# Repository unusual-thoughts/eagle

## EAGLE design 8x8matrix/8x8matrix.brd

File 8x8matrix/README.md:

Backpack for 8x8 RGB LED matrix
==============================

This is a simple breakout board for 8x8 RGB matrices like the [GTM2088ARGB](http://www.ebay.com/itm/5mm-8x8-Matrix-RGB-LED-Common-Anode-Full-Colour-60-60mm-/370699782315)  
It uses TLC5947 that provides 24 12 bit current sink PWM channels, and a 74HC138 3 to 8 line decoder followed by P-channel MOSFETs to drive the rows.
The parts are in the ../mylibs/mylib.lbr library.  
The whole thing fits on a single layer PCB.  
The matrix is controlled through the 9-pin header with this pinout:

Pin number	| Label	| Description
----------	| -----	| -----------
1			| A2	| row higher bit
2			| A1	| row middle bit
3			| A0	| row lower bit
4			| SIN	| TLC data (24x12 bit = 36 bytes)
5			| SCLK	| TLC clock
6			| BLANK	| TLC blank columns and reset PWM timer
7			| GND	| Ground
8			| VCC	| +5V
9			| XLAT	| TLC latch data

To get everything to fit on a single sided board, I had to make weird column and row assignments:

A0	| A1	| A2	| Row Number
--- | ---	| ---	| ----------
0	| 0		| 0		| 2
0	| 0		| 1		| 1
0	| 1		| 0		| 0
0	| 1		| 1		| 7
1	| 0		| 0		| 4
1	| 0		| 1		| 5
1	| 1		| 0		| 6
1	| 1		| 1		| 3

TLC channel	| Columns
----------  | ------
0-7			| Red 0-7
8-15		| Blue 0-7
16-23		| Green 7-0 (inverted order)

There is a modified version of the Tlc5940 library by Alex Leone, named Tlc5947 in my arduino folder. Like its counterpart, it can use arduino hardware spi to speed things up to an acceptable refresh rate. The basic bitbang code flickers quite a bit, even with direct port manipulation.

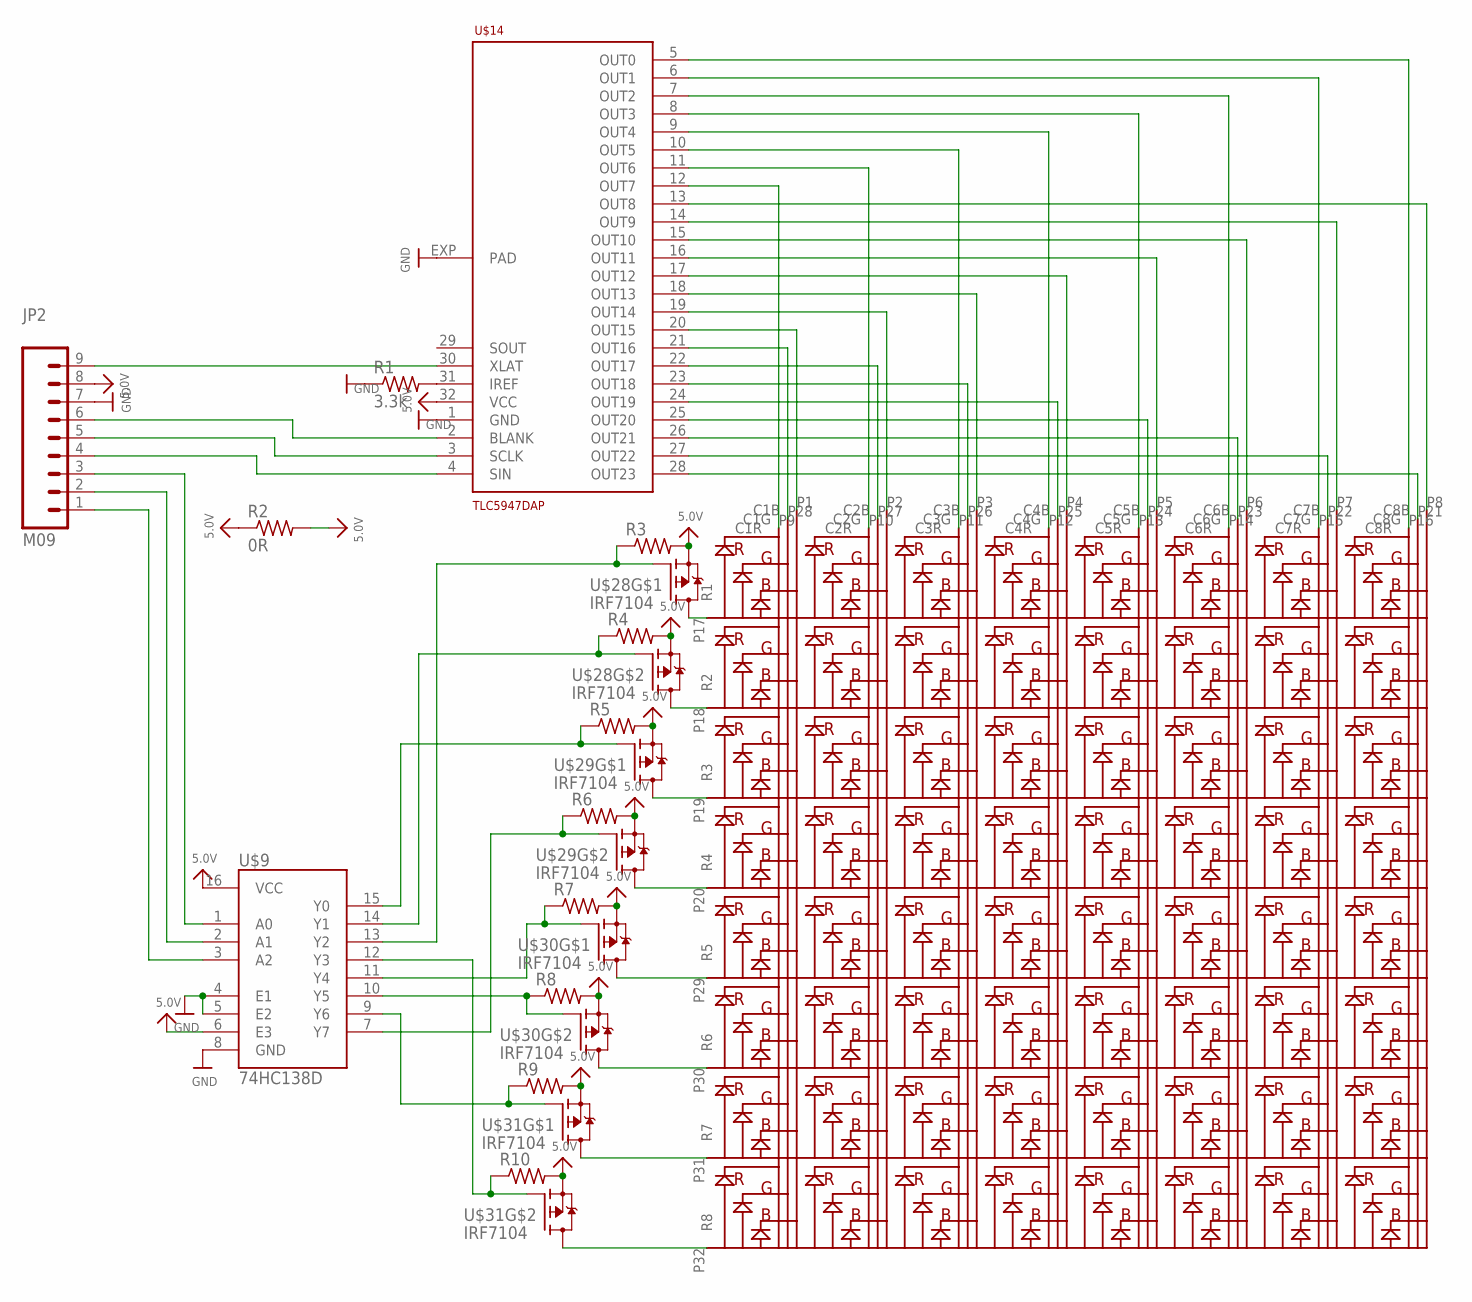
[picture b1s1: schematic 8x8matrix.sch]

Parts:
JP2: M09; 1X09
R1: 3.3k; R0805
R2: 0R; M1206
R3, R4, R5, R6, R7, R8, R9, R10: R-US_R0805; R0805
U$1: GTM2088ARGB; 8X8MATRIX
U$9: 74HC138D; SO-16
U$14: TLC5947DAP; HTSSOP32DAP
U$28, U$29, U$30, U$31: IRF7104; SOIC8

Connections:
5.0V: JP2.8, R2.1, R2.2, R3.2, R4.2, R5.2, R6.2, R7.2, R8.2, R9.2, R10.2, U$9.6 (E3), U$9.16 (VCC), U$14.32 (VCC), U$28.1 (S), U$28.3 (S), U$29.1 (S), U$29.3 (S), U$30.1 (S), U$30.3 (S), U$31.1 (S), U$31.3 (S)
BLANK: JP2.6, U$14.2 (BLANK)
GND: JP2.7, R1.1, U$9.4 (E1), U$9.5 (E2), U$9.8 (GND), U$14.1 (GND), U$14.EXP (PAD)
unnamed: U$1.P16 (C8R), U$14.5 (OUT0)
unnamed: U$1.P15 (C7R), U$14.6 (OUT1)
unnamed: U$1.P14 (C6R), U$14.7 (OUT2)
unnamed: U$1.P13 (C5R), U$14.8 (OUT3)
unnamed: U$1.P12 (C4R), U$14.9 (OUT4)
unnamed: U$1.P11 (C3R), U$14.10 (OUT5)
unnamed: U$1.P10 (C2R), U$14.11 (OUT6)
unnamed: U$1.P9 (C1R), U$14.12 (OUT7)
unnamed: U$1.P8 (C8B), U$14.13 (OUT8)
unnamed: U$1.P7 (C7B), U$14.14 (OUT9)
unnamed: U$1.P6 (C6B), U$14.15 (OUT10)
unnamed: U$1.P5 (C5B), U$14.16 (OUT11)
unnamed: U$1.P4 (C4B), U$14.17 (OUT12)
unnamed: U$1.P3 (C3B), U$14.18 (OUT13)
unnamed: U$1.P2 (C2B), U$14.19 (OUT14)
unnamed: U$1.P1 (C1B), U$14.20 (OUT15)
unnamed: U$1.P28 (C1G), U$14.21 (OUT16)
unnamed: U$1.P27 (C2G), U$14.22 (OUT17)
unnamed: U$1.P26 (C3G), U$14.23 (OUT18)
unnamed: U$1.P25 (C4G), U$14.24 (OUT19)
unnamed: U$1.P24 (C5G), U$14.25 (OUT20)
unnamed: U$1.P23 (C6G), U$14.26 (OUT21)
unnamed: U$1.P22 (C7G), U$14.27 (OUT22)
unnamed: U$1.P21 (C8G), U$14.28 (OUT23)
unnamed: R1.2, U$14.31 (IREF)
unnamed: U$1.P19 (R3), U$29.7 (D), U$29.8 (D)
unnamed: U$1.P18 (R2), U$28.5 (D), U$28.6 (D)
unnamed: JP2.3, U$9.1 (A0)
unnamed: JP2.2, U$9.2 (A1)
unnamed: JP2.1, U$9.3 (A2)
unnamed: U$1.P17 (R1), U$28.7 (D), U$28.8 (D)
unnamed: U$1.P29 (R5), U$30.7 (D), U$30.8 (D)
unnamed: U$1.P31 (R7), U$31.7 (D), U$31.8 (D)
unnamed: U$1.P20 (R4), U$29.5 (D), U$29.6 (D)
unnamed: U$1.P30 (R6), U$30.5 (D), U$30.6 (D)
unnamed: U$1.P32 (R8), U$31.5 (D), U$31.6 (D)
SCLK: JP2.5, U$14.3 (SCLK)
SIN: JP2.4, U$14.4 (SIN)
XLAT: JP2.9, U$14.30 (XLAT)
Y0: R5.1, U$9.15 (Y0), U$29.2 (G)
Y1: R4.1, U$9.14 (Y1), U$28.4 (G)
Y2: R3.1, U$9.13 (Y2), U$28.2 (G)
Y3: R10.1, U$9.12 (Y3), U$31.4 (G)
Y4: R7.1, U$9.11 (Y4), U$30.2 (G)
Y5: R8.1, U$9.10 (Y5), U$30.4 (G)
Y6: R9.1, U$9.9 (Y6), U$31.2 (G)
Y7: R6.1, U$9.7 (Y7), U$29.4 (G)

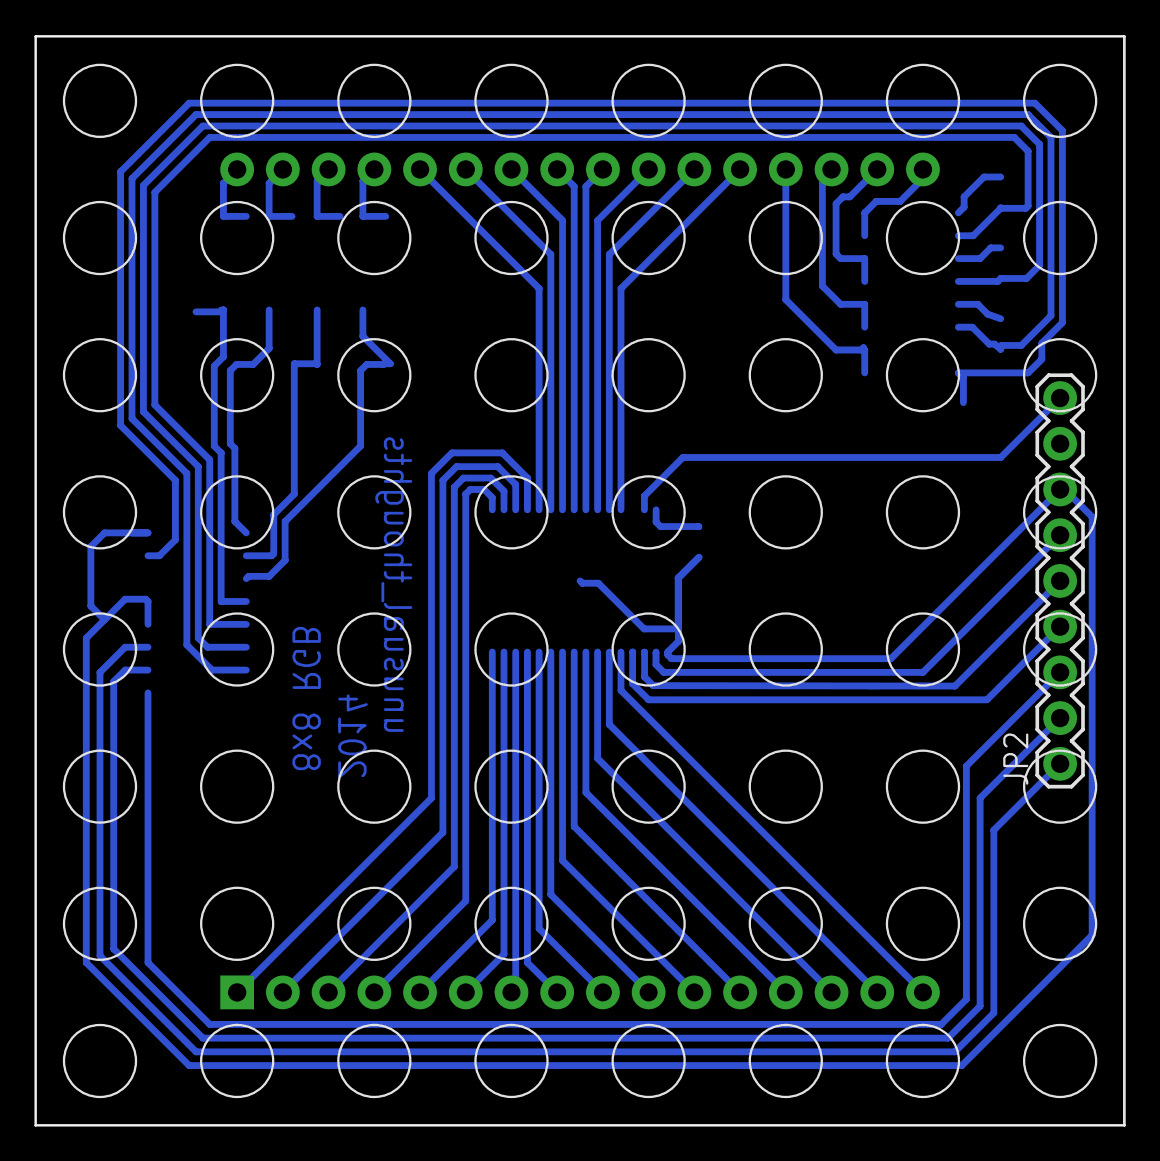
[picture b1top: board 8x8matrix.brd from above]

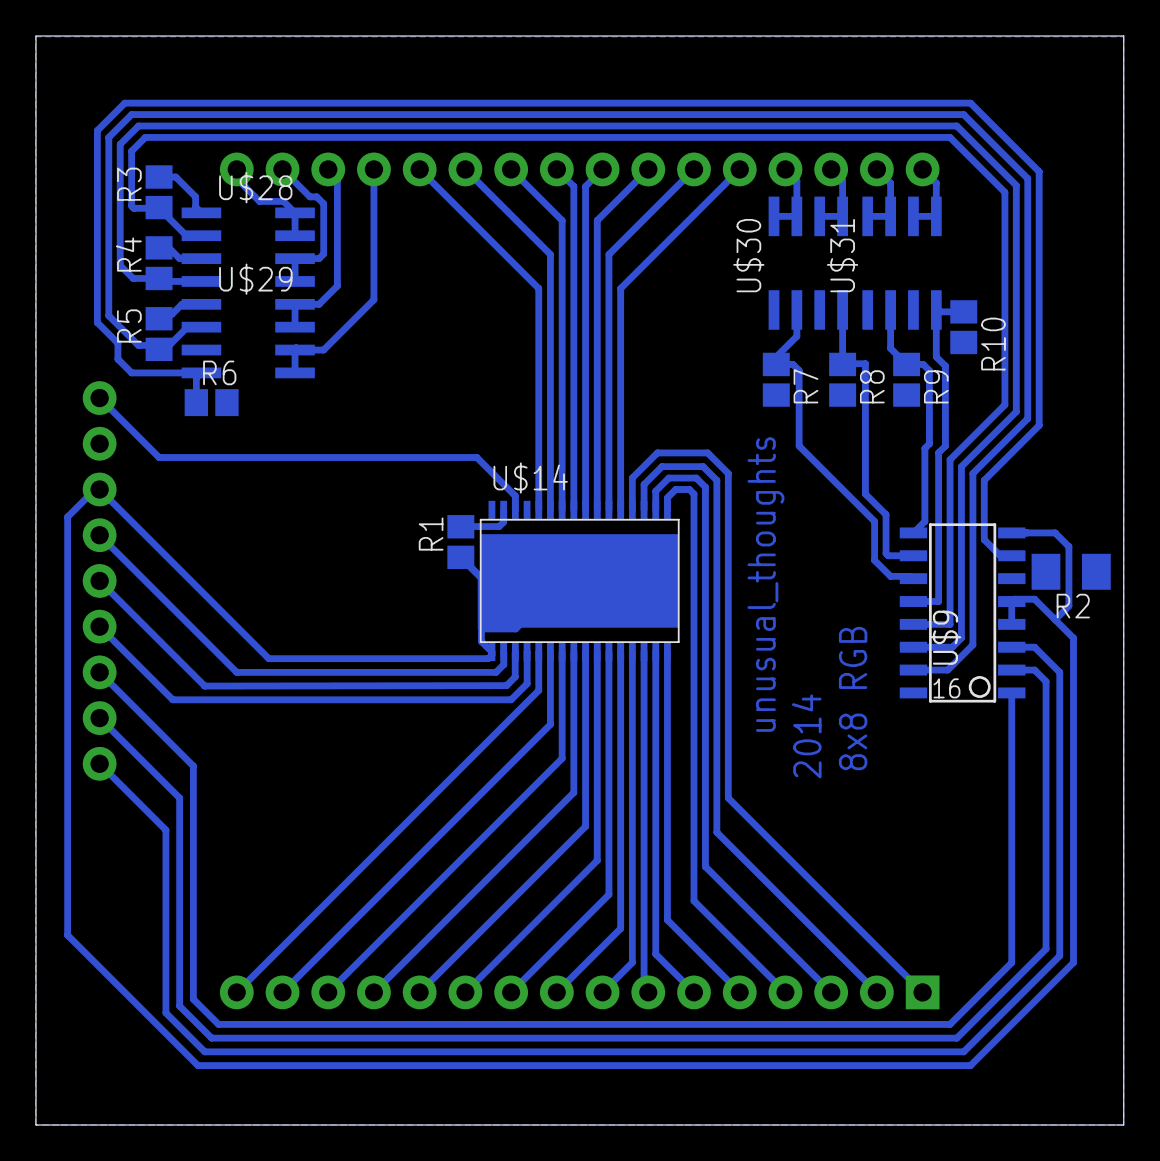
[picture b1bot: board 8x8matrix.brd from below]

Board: 2 copper layers, 60.4 x 60.5 mm, 18 parts (16 on the bottom side), 50 nets.

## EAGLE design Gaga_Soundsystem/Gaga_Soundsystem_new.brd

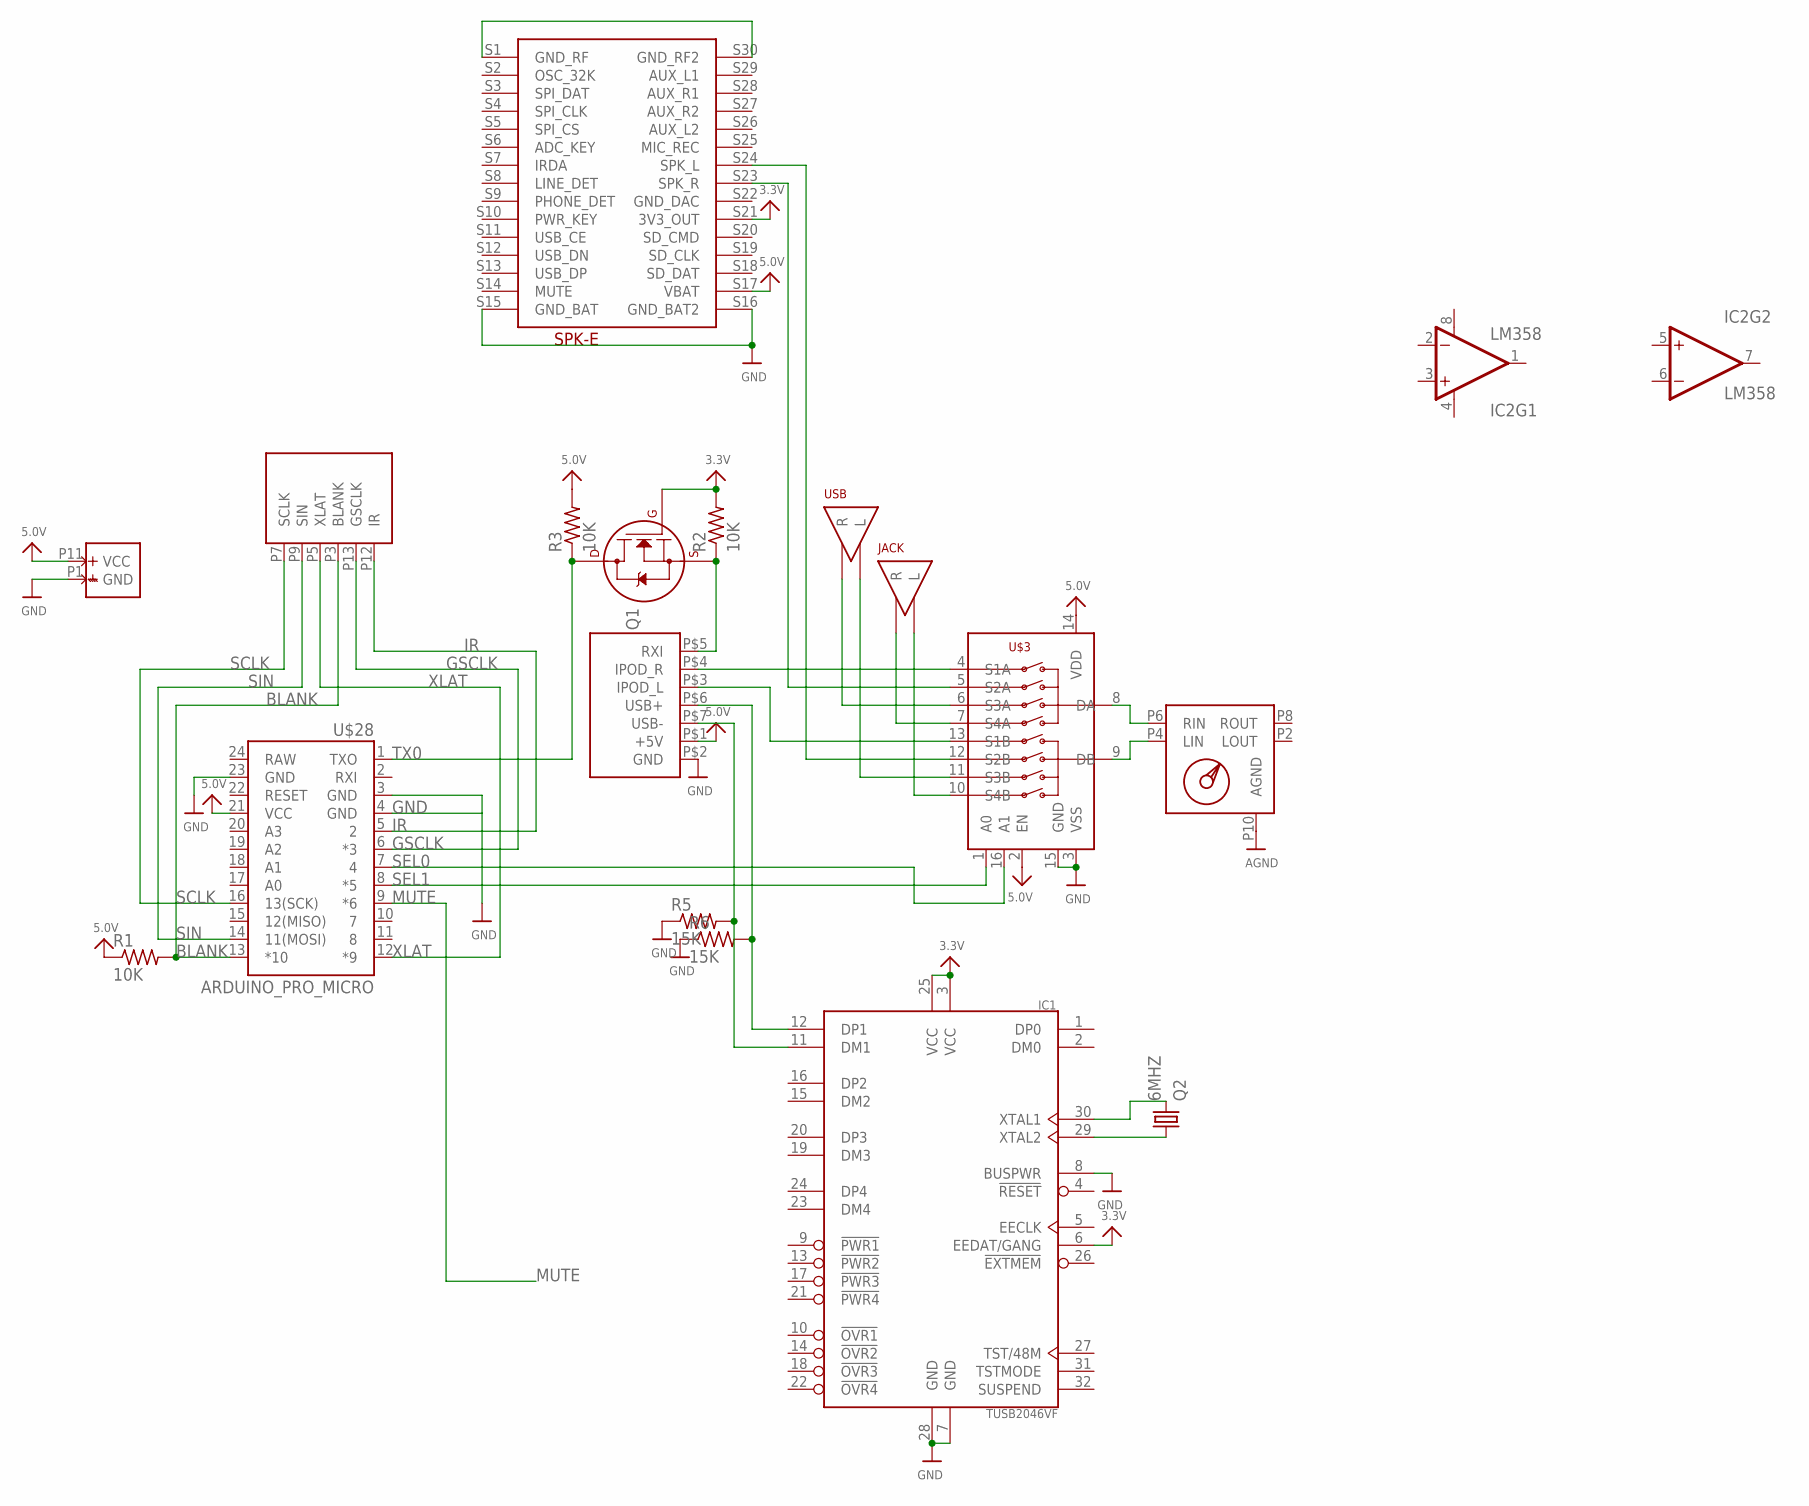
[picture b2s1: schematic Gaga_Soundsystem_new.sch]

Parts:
IC1: TUSB2046VF; TQFP32-08
IC2: LM358; DIP08
JACK: JACK; AUDIOCON
Q1: 2N7000_TO92; TO-92
Q2: 6MHZ; HC49/S
R1: 10K; 0207/7
R2: 10K; M0805
R3: 10K; R0805
R5, R6: 15K; R0805
U$1: OTHERSIDE
U$3: ADG709; TSSOP16
U$5: IPODCON
U$7: SPK-E
U$28: ARDUINO_PRO_MICRO
USB: USB; AUDIOCON

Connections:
3.3V: IC1.3 (VCC), IC1.6 (EEDAT/GANG), IC1.25 (VCC), Q1.2 (G), R2.2, U$7.S21 (3V3_OUT)
5.0V: R1.1, R3.2, U$1.P11 (VCC), U$3.2 (EN), U$3.14 (VDD), U$5.P$1 (+5V), U$7.S17 (VBAT), U$28.21 (VCC)
AGND: U$1.P10 (AGND)
BLANK: R1.2, U$1.P3 (BLANK), U$28.13 (*10)
BLUL: U$3.12 (S2B), U$7.S24 (SPK_L)
BLUR: U$3.5 (S2A), U$7.S23 (SPK_R)
GND: IC1.7 (GND), IC1.8 (BUSPWR), IC1.28 (GND), R5.1, R6.1, U$1.P1 (GND), U$3.3 (VSS), U$3.15 (GND), U$5.P$2 (GND), U$7.S15 (GND_BAT), U$7.S16 (GND_BAT2), U$28.3 (GND), U$28.4 (GND), U$28.23 (GND)
GND_RF: U$7.S1 (GND_RF), U$7.S30 (GND_RF2)
GSCLK: U$1.P13 (GSCLK), U$28.6 (*3)
IPODL: U$3.13 (S1B), U$5.P$3 (IPOD_L)
IPODR: U$3.4 (S1A), U$5.P$4 (IPOD_R)
IR: U$1.P12 (IR), U$28.5 (2)
JACKL: JACK.P$2 (L), U$3.10 (S4B)
JACKR: JACK.P$1 (R), U$3.7 (S4A)
LIN: U$1.P4 (LIN), U$3.9 (DB)
MUTE: U$28.9 (*6)
unnamed: Q1.1 (S), R2.1, U$5.P$5 (RXI)
unnamed: IC1.29 (XTAL2), Q2.1
unnamed: IC1.30 (XTAL1), Q2.2
unnamed: IC1.12 (DP1), R6.2, U$5.P$6 (USB+)
unnamed: IC1.11 (DM1), R5.2, U$5.P$7 (USB-)
RIN: U$1.P6 (RIN), U$3.8 (DA)
SCLK: U$1.P7 (SCLK), U$28.16 (13(SCK))
SEL0: U$3.16 (A1), U$28.7 (4)
SEL1: U$3.1 (A0), U$28.8 (*5)
SIN: U$1.P9 (SIN), U$28.14 (11(MOSI))
TX0: Q1.3 (D), R3.1, U$28.1 (TXO)
USBL: U$3.11 (S3B), USB.P$2 (L)
USBR: U$3.6 (S3A), USB.P$1 (R)
V+: IC2.8 (V+)
V-: IC2.4 (V-)
XLAT: U$1.P5 (XLAT), U$28.12 (*9)

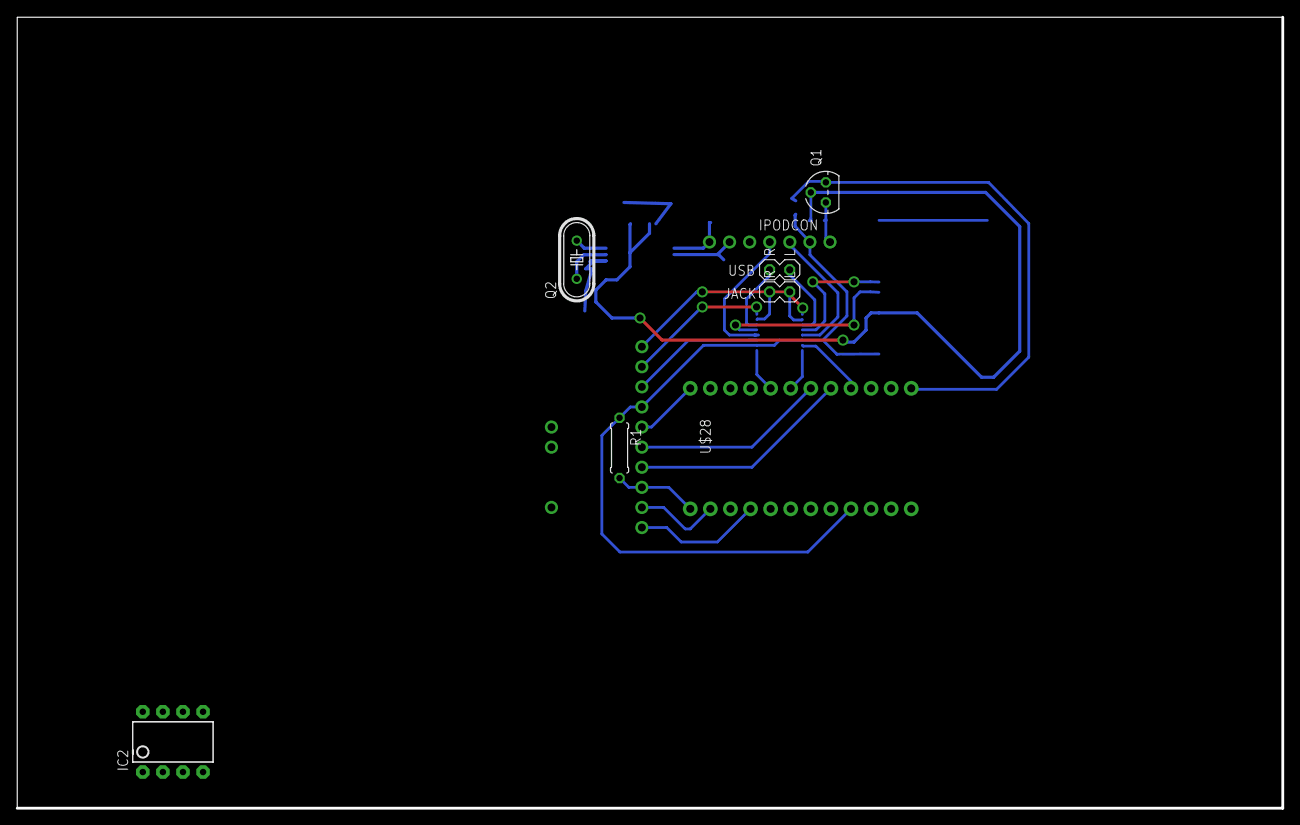
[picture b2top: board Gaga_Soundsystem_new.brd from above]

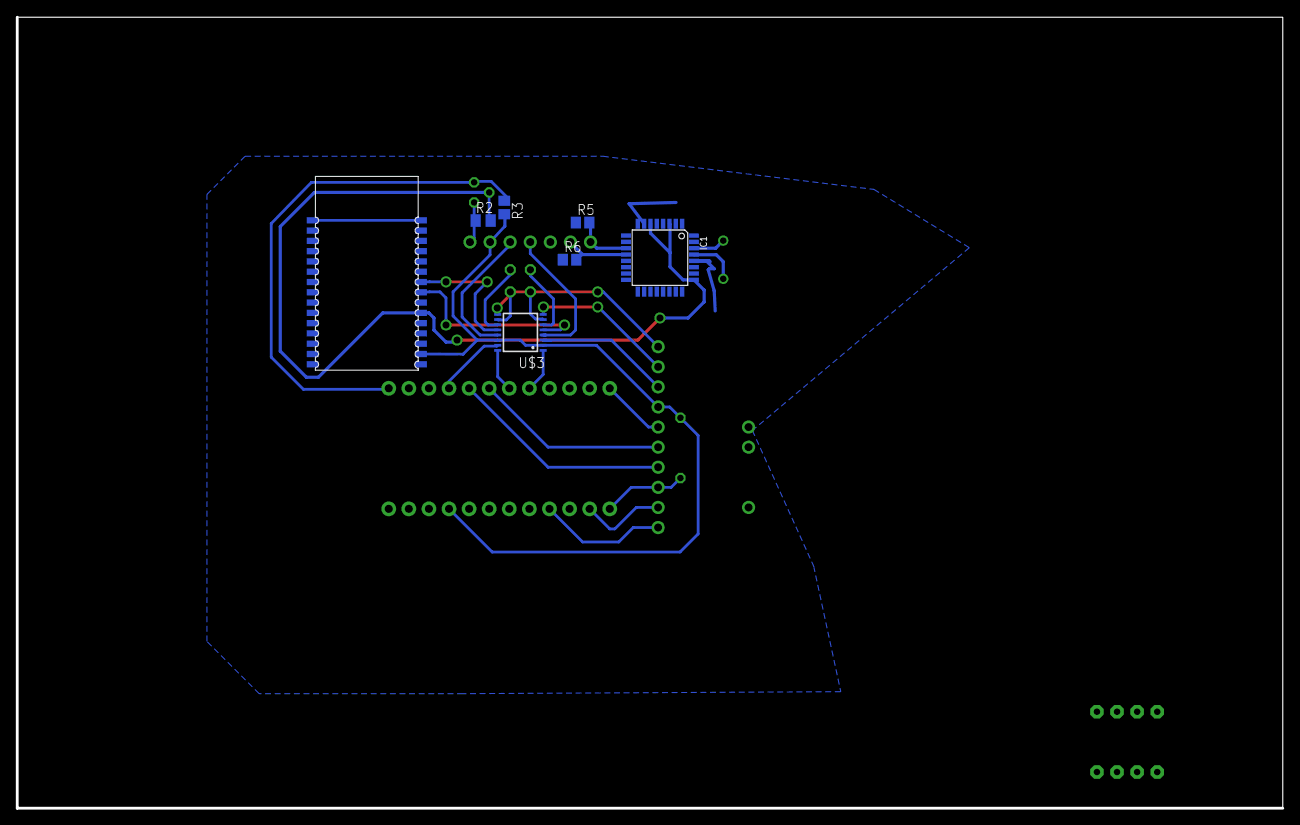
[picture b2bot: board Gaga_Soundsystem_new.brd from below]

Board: 2 copper layers, 160.0 x 100.0 mm, 16 parts (7 on the bottom side), 28 nets.

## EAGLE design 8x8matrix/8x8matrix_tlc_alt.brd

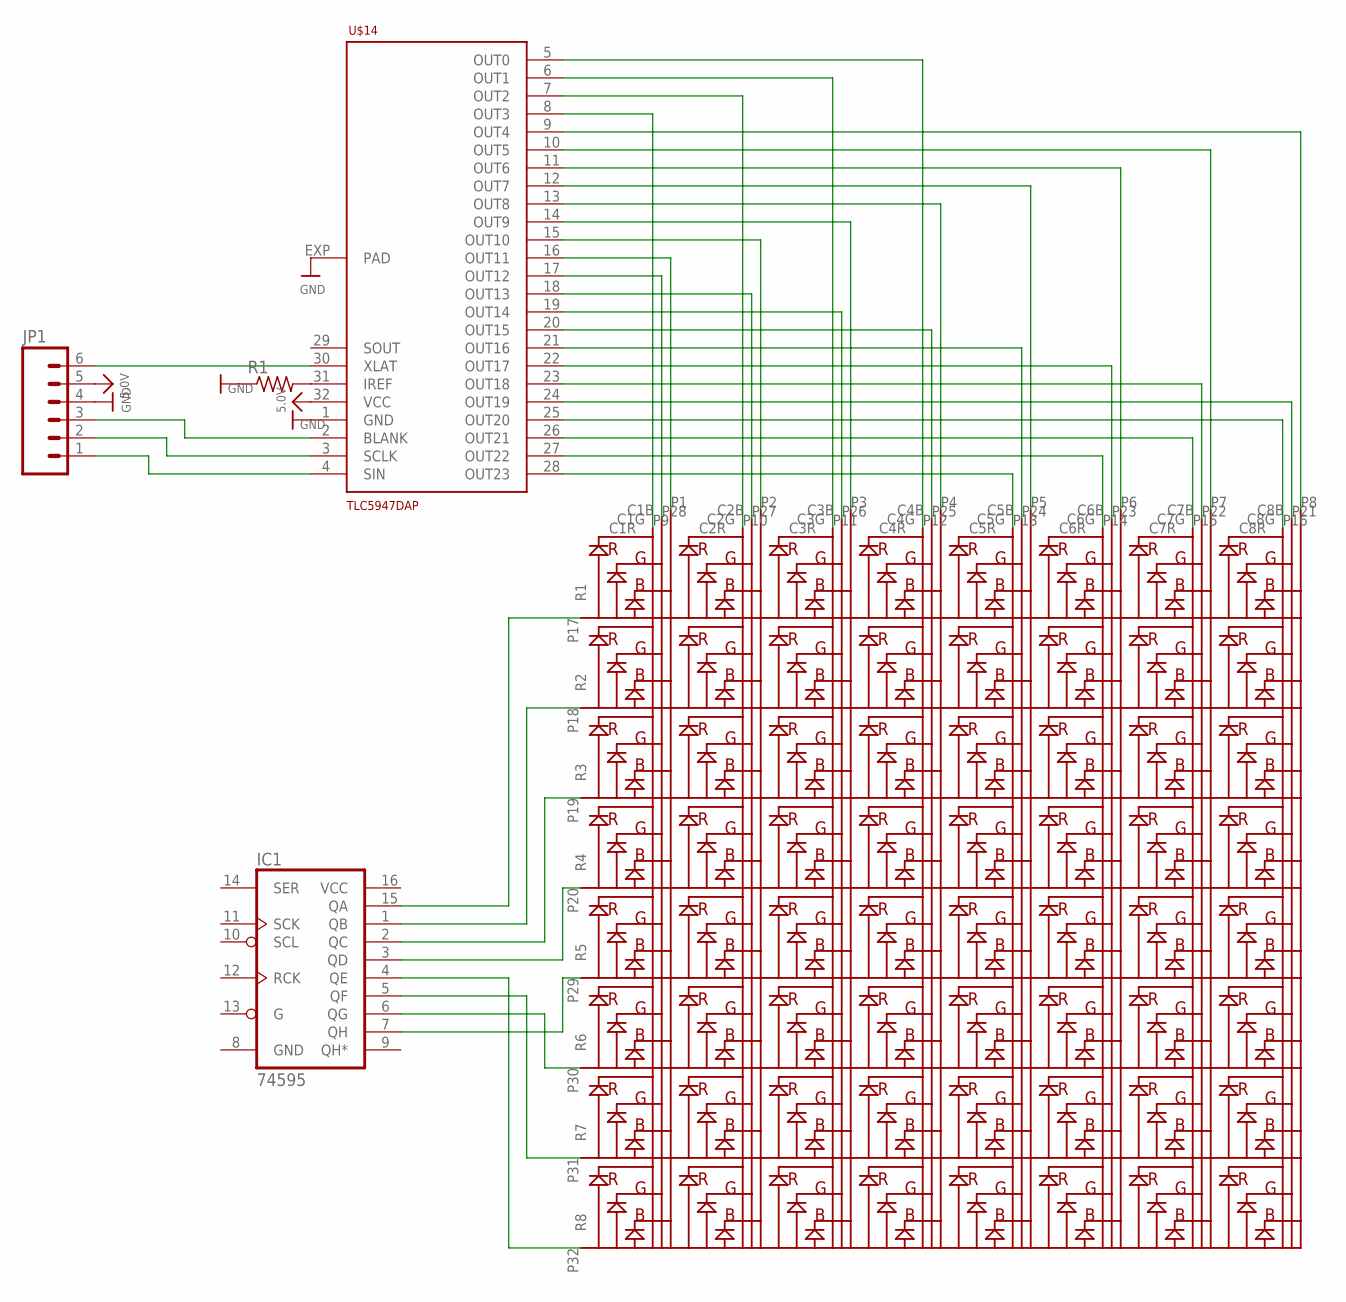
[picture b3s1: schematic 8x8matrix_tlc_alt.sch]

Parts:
IC1: 74595; TSSOP16
JP1: M06SIP; 1X06
R1: R-US_R0805; R0805
U$1: GTM2088ARGB; 8X8MATRIX
U$14: TLC5947DAP; HTSSOP32DAP

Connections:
5.0V: JP1.5, U$14.32 (VCC)
BLANK: JP1.3, U$14.2 (BLANK)
GND: IC1.8 (GND), JP1.4, R1.1, U$14.1 (GND), U$14.EXP (PAD)
unnamed: U$1.P1 (C1B), U$14.16 (OUT11)
unnamed: U$1.P2 (C2B), U$14.15 (OUT10)
unnamed: U$1.P3 (C3B), U$14.14 (OUT9)
unnamed: U$1.P4 (C4B), U$14.13 (OUT8)
unnamed: U$1.P5 (C5B), U$14.12 (OUT7)
unnamed: U$1.P6 (C6B), U$14.11 (OUT6)
unnamed: U$1.P7 (C7B), U$14.10 (OUT5)
unnamed: U$1.P8 (C8B), U$14.9 (OUT4)
unnamed: U$1.P9 (C1R), U$14.8 (OUT3)
unnamed: U$1.P10 (C2R), U$14.7 (OUT2)
unnamed: U$1.P11 (C3R), U$14.6 (OUT1)
unnamed: U$1.P12 (C4R), U$14.5 (OUT0)
unnamed: U$1.P13 (C5R), U$14.28 (OUT23)
unnamed: U$1.P14 (C6R), U$14.27 (OUT22)
unnamed: U$1.P15 (C7R), U$14.26 (OUT21)
unnamed: U$1.P16 (C8R), U$14.25 (OUT20)
unnamed: U$1.P28 (C1G), U$14.17 (OUT12)
unnamed: U$1.P27 (C2G), U$14.18 (OUT13)
unnamed: U$1.P26 (C3G), U$14.19 (OUT14)
unnamed: U$1.P25 (C4G), U$14.20 (OUT15)
unnamed: U$1.P24 (C5G), U$14.21 (OUT16)
unnamed: U$1.P23 (C6G), U$14.22 (OUT17)
unnamed: U$1.P22 (C7G), U$14.23 (OUT18)
unnamed: U$1.P21 (C8G), U$14.24 (OUT19)
unnamed: IC1.7 (QH), U$1.P29 (R5)
unnamed: IC1.1 (QB), U$1.P18 (R2)
unnamed: R1.2, U$14.31 (IREF)
unnamed: JP1.2, U$14.3 (SCLK)
unnamed: IC1.15 (QA), U$1.P17 (R1)
unnamed: IC1.6 (QG), U$1.P30 (R6)
unnamed: IC1.2 (QC), U$1.P19 (R3)
unnamed: IC1.3 (QD), U$1.P20 (R4)
unnamed: IC1.5 (QF), U$1.P31 (R7)
unnamed: IC1.4 (QE), U$1.P32 (R8)
SIN: JP1.1, U$14.4 (SIN)
VCC: IC1.16 (VCC)
XLAT: JP1.6, U$14.30 (XLAT)

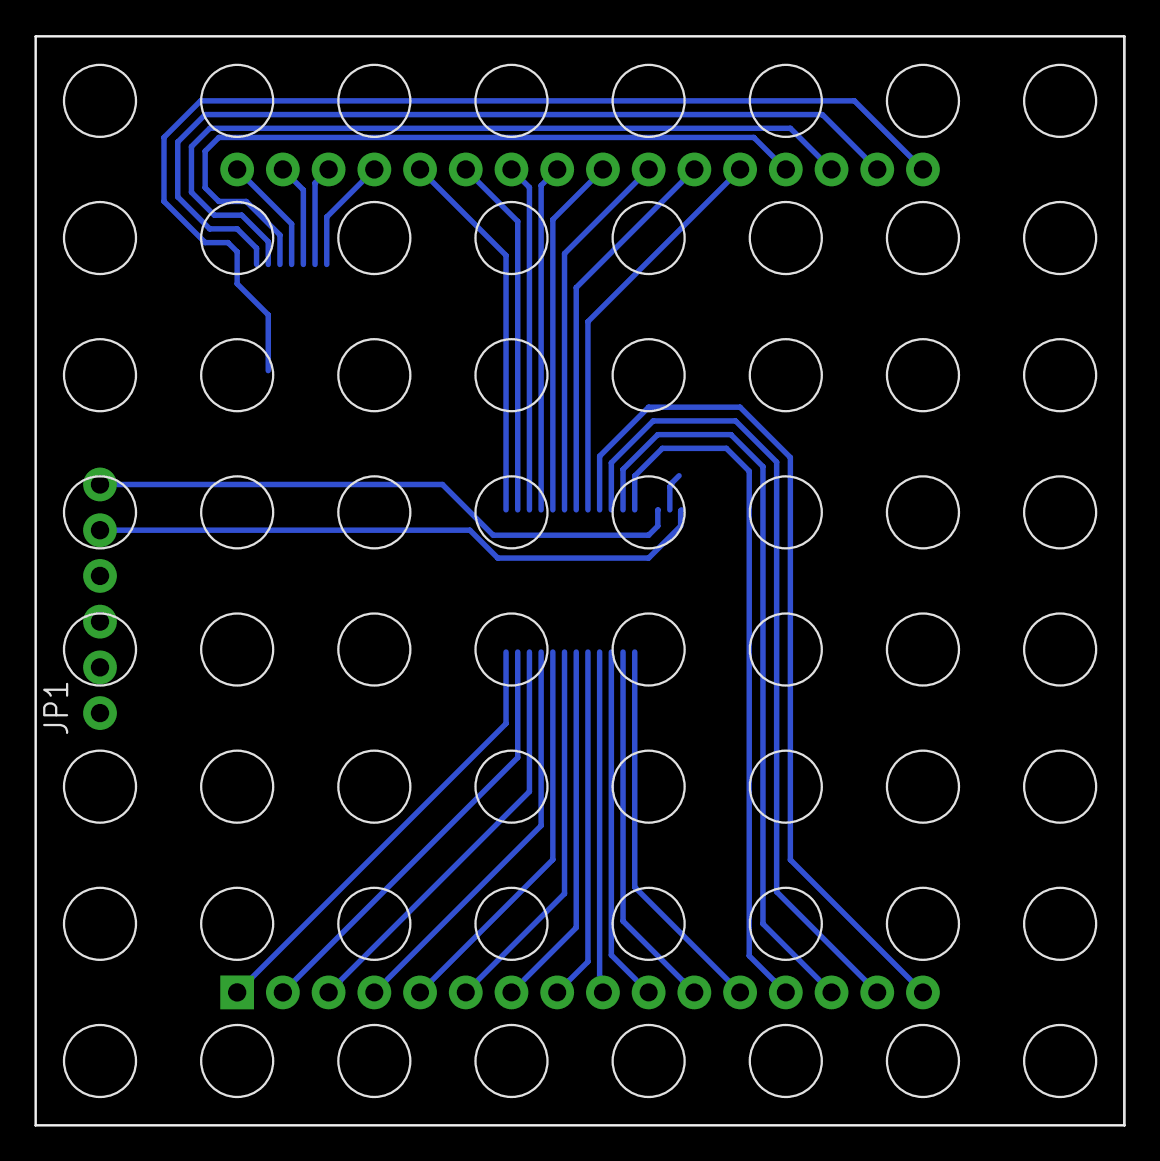
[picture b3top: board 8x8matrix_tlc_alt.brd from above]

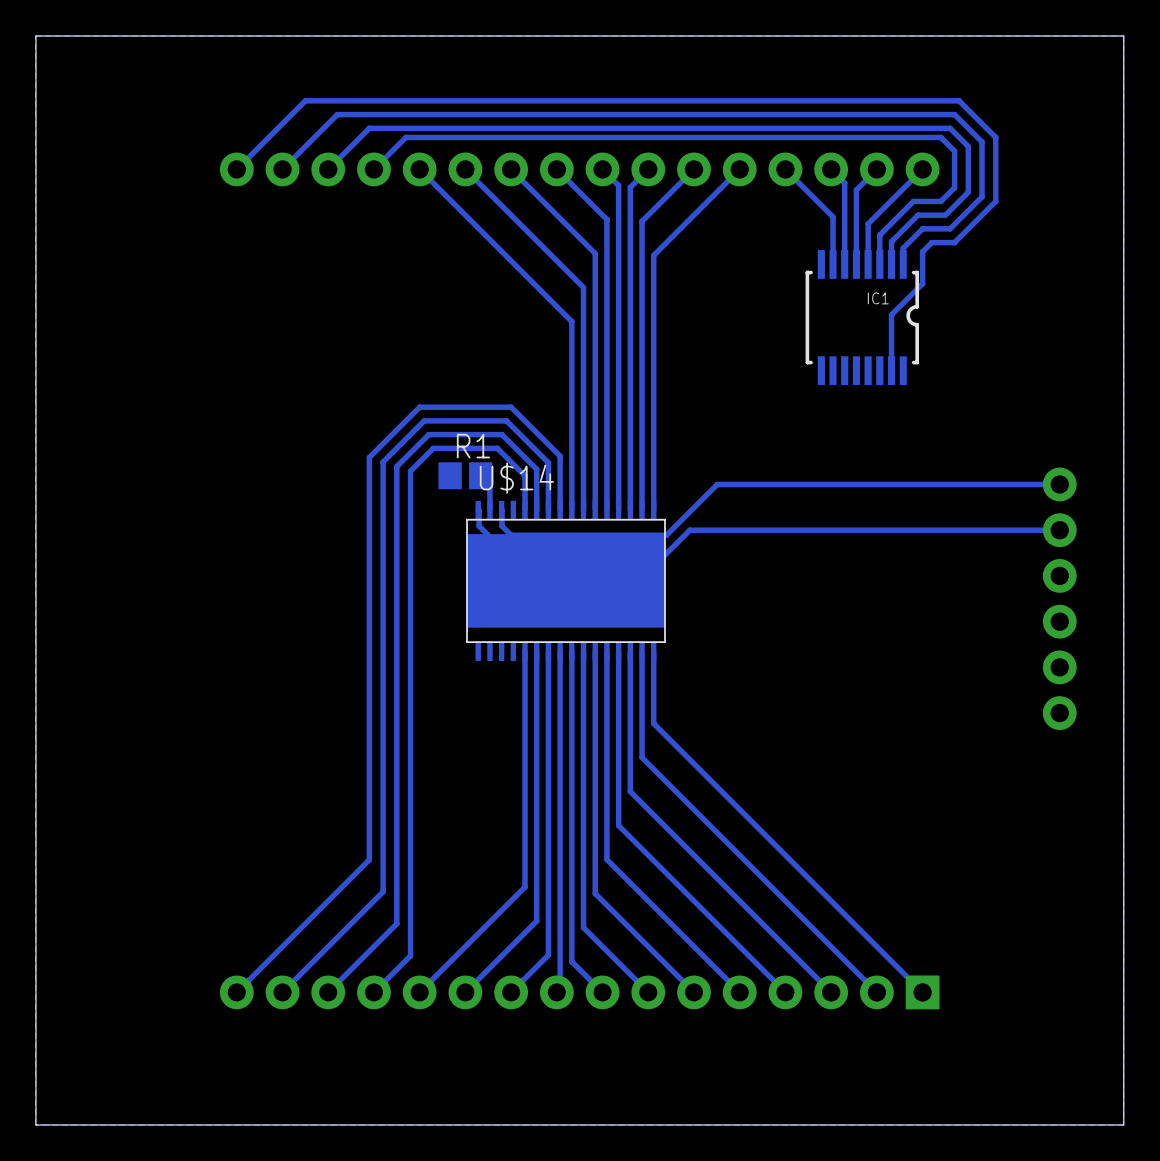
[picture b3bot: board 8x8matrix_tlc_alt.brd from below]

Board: 2 copper layers, 60.4 x 60.5 mm, 5 parts (3 on the bottom side), 39 nets.

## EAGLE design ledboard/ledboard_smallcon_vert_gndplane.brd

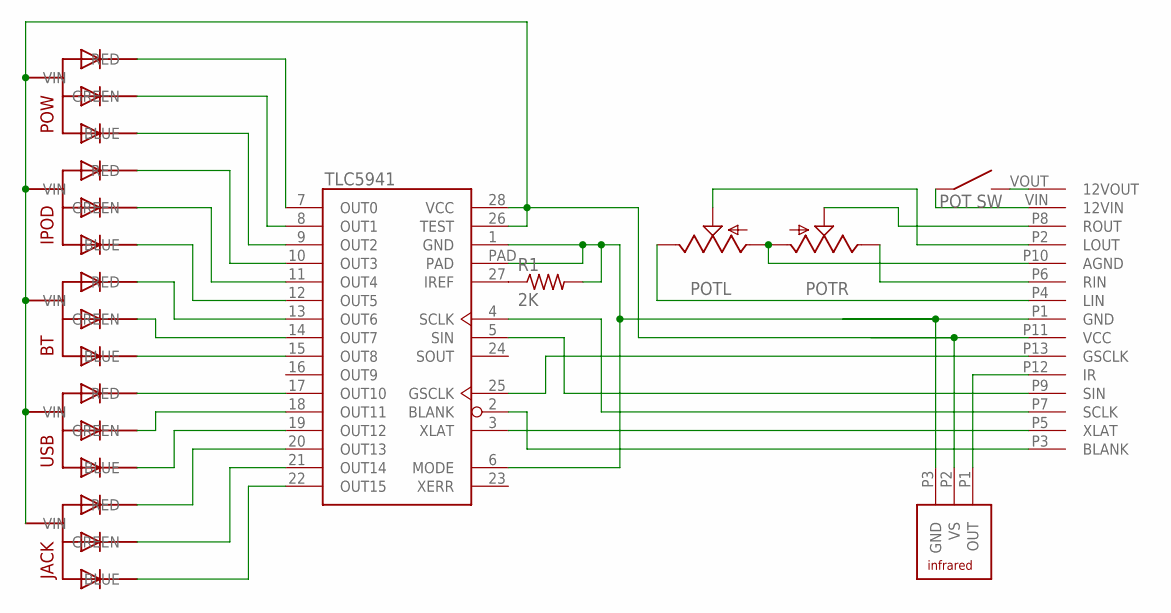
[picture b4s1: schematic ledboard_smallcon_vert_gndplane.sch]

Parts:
BT: 5MMRGBLEDBENT; BENTLED
IPOD: 5MMRGBLEDBENT; BENTLED
IR: TSOP323
JACK: 5MMRGBLEDBENT; BENTLED
POT: ALPS_RK0971221Z0N; ALPS_RK0971221Z0X
POW: 5MMRGBLEDBENT; BENTLED
R1: 2K; 0207/7
U$1: TLC5941; HTSSOP28_POWERPAD
U$3: CONNECTORSMALL4; SMALLL4
USB: 5MMRGBLEDBENT; BENTLED

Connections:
12VIN: POT.S1, U$3.VIN (12VIN)
12VOUT: POT.S2, U$3.VOUT (12VOUT)
AGND: POT.G1 (1), POT.G2 (1), U$3.P10 (AGND)
BLANK: U$1.2 (BLANK), U$3.P3 (BLANK)
GND: IR.P3 (GND), R1.2, U$1.1 (GND), U$1.6 (MODE), U$1.PAD, U$3.P1 (GND)
GSCLK: U$1.25 (GSCLK), U$3.P13 (GSCLK)
IR: IR.P1 (OUT), U$3.P12 (IR)
LIN: POT.I1 (3), U$3.P4 (LIN)
LOUT: POT.O1 (2), U$3.P2 (LOUT)
N1: POW.P$1 (BLUE), U$1.9 (OUT2)
unnamed: POW.P$4 (RED), U$1.7 (OUT0)
unnamed: POW.P$2 (GREEN), U$1.8 (OUT1)
unnamed: IPOD.P$4 (RED), U$1.10 (OUT3)
unnamed: IPOD.P$2 (GREEN), U$1.11 (OUT4)
unnamed: IPOD.P$1 (BLUE), U$1.12 (OUT5)
unnamed: BT.P$4 (RED), U$1.13 (OUT6)
unnamed: BT.P$1 (BLUE), U$1.15 (OUT8)
unnamed: U$1.19 (OUT12), USB.P$1 (BLUE)
unnamed: JACK.P$1 (BLUE), U$1.22 (OUT15)
unnamed: BT.P$2 (GREEN), U$1.14 (OUT7)
unnamed: U$1.17 (OUT10), USB.P$4 (RED)
unnamed: JACK.P$4 (RED), U$1.20 (OUT13)
unnamed: U$1.18 (OUT11), USB.P$2 (GREEN)
unnamed: JACK.P$2 (GREEN), U$1.21 (OUT14)
unnamed: R1.1, U$1.27 (IREF)
RIN: POT.I2 (3), U$3.P6 (RIN)
ROUT: POT.O2 (2), U$3.P8 (ROUT)
SCLK: U$1.4 (SCLK), U$3.P7 (SCLK)
SIN: U$1.5 (SIN), U$3.P9 (SIN)
VCC: BT.P$3 (VIN), IPOD.P$3 (VIN), IR.P2 (VS), JACK.P$3 (VIN), POW.P$3 (VIN), U$1.26 (TEST), U$1.28 (VCC), U$3.P11 (VCC), USB.P$3 (VIN)
XLAT: U$1.3 (XLAT), U$3.P5 (XLAT)

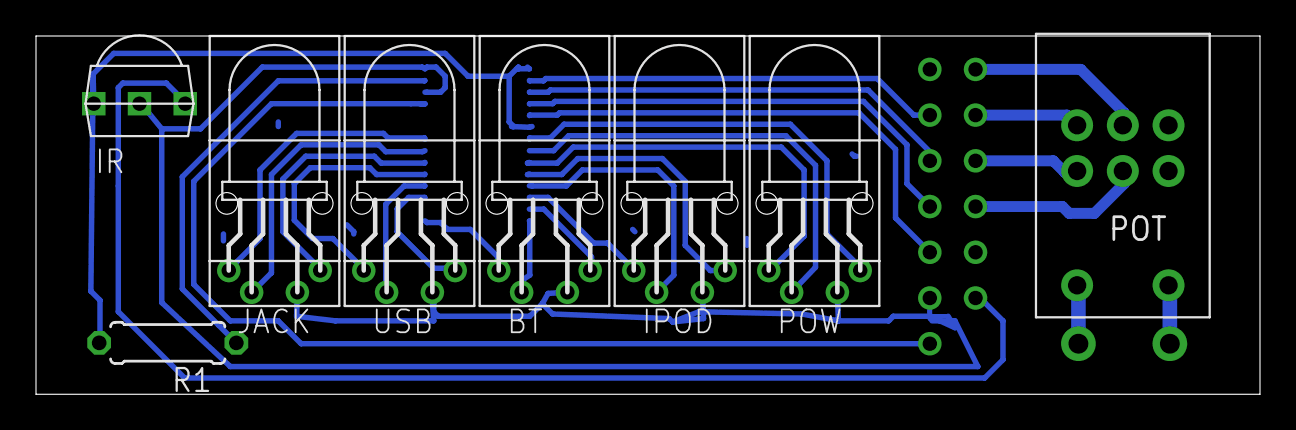
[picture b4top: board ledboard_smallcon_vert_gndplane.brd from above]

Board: 2 copper layers, 68.0 x 19.9 mm, 10 parts (1 on the bottom side), 31 nets.

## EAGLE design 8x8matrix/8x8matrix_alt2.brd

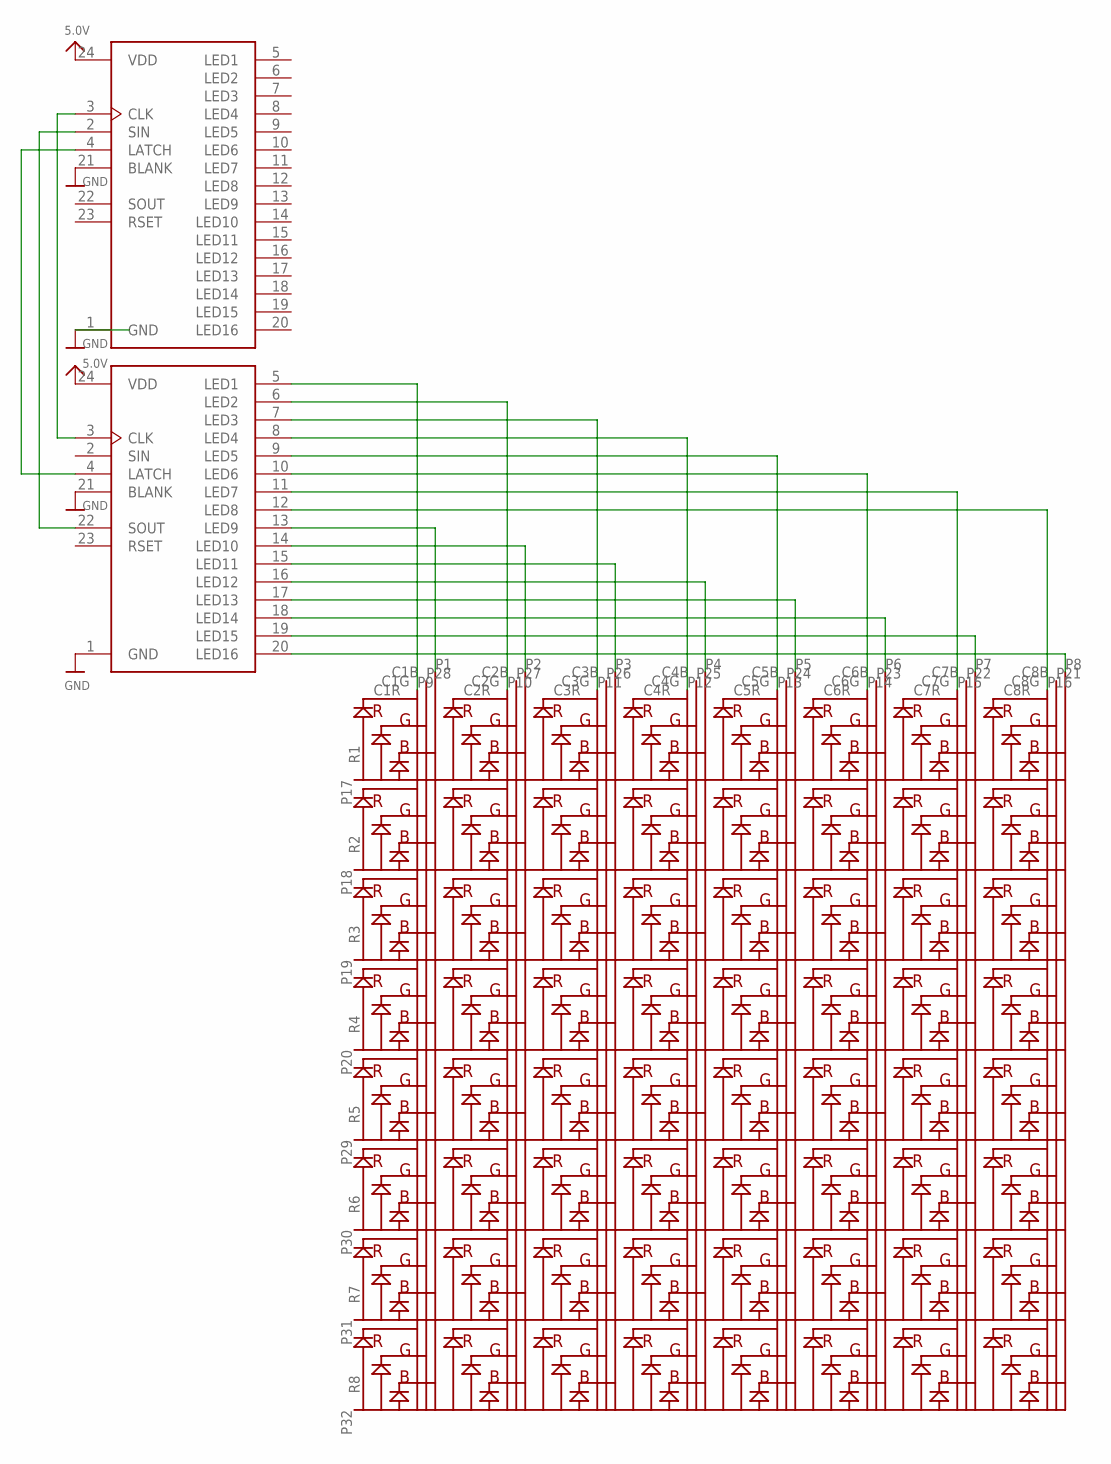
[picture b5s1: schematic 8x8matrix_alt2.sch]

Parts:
U$1: GTM2088ARGB; 8X8MATRIX
U$2, U$3: CAT4016W; TSSOP24

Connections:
5.0V: U$2.24 (VDD), U$3.24 (VDD)
GND: U$2.1 (GND), U$2.21 (BLANK), U$3.1 (GND), U$3.21 (BLANK)
unnamed: U$1.P9 (C1R), U$3.5 (LED1)
unnamed: U$1.P10 (C2R), U$3.6 (LED2)
unnamed: U$1.P11 (C3R), U$3.7 (LED3)
unnamed: U$1.P12 (C4R), U$3.8 (LED4)
unnamed: U$1.P13 (C5R), U$3.9 (LED5)
unnamed: U$1.P14 (C6R), U$3.10 (LED6)
unnamed: U$1.P15 (C7R), U$3.11 (LED7)
unnamed: U$1.P16 (C8R), U$3.12 (LED8)
unnamed: U$1.P1 (C1B), U$3.13 (LED9)
unnamed: U$1.P2 (C2B), U$3.14 (LED10)
unnamed: U$1.P3 (C3B), U$3.15 (LED11)
unnamed: U$1.P4 (C4B), U$3.16 (LED12)
unnamed: U$1.P5 (C5B), U$3.17 (LED13)
unnamed: U$1.P6 (C6B), U$3.18 (LED14)
unnamed: U$1.P7 (C7B), U$3.19 (LED15)
unnamed: U$1.P8 (C8B), U$3.20 (LED16)
unnamed: U$2.3 (CLK), U$3.3 (CLK)
unnamed: U$2.2 (SIN), U$3.22 (SOUT)
unnamed: U$2.4 (LATCH), U$3.4 (LATCH)

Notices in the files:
parts and their libraries:
SparkFun-Connectors: Licensing: Creative Commons ShareAlike 4.0 International - https://creativecommons.org/licenses/by-sa/4.0
microbuilder: This work is placed in the public domain, and may be freely used for commercial and non-commercial work with the following conditions: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
